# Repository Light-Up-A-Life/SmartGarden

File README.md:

# SmartGarden
Smart Garden development for the Light Up A Life project

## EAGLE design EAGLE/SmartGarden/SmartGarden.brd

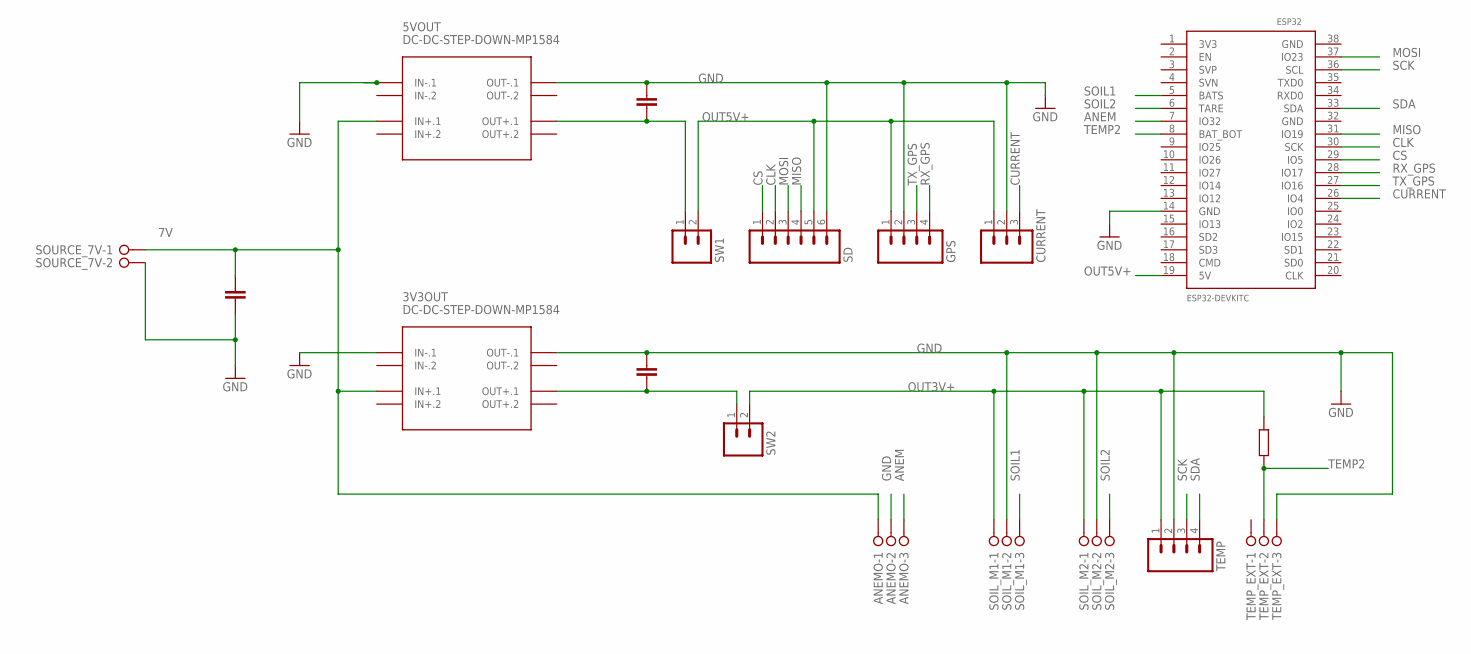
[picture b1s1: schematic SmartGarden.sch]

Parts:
3V3OUT, 5VOUT: DC-DC-STEP-DOWN-MP1584
ANEMO: W237-3E
C3V, C5V, C7V: C-EU025-025X050; C025-025X050
CURRENT: M03; 03P
ESP32: ESP32DEVKITC; ESP32-DEVKITC
GPS: M04; 04P
R1: R-EU_0204/7; 0204/7
SD: M06; 06P
SOIL_M1, SOIL_M2: W237-3E
SOURCE_7V: W237-02P; W237-132
SW1, SW2: M02; 02P
TEMP: M04; 04P
TEMP_EXT: W237-3E

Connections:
7V: 3V3OUT.IN+.1, 5VOUT.IN+.1, ANEMO.1, C7V.1, SOURCE_7V.1
ANEM: ANEMO.3, ESP32.7 (IO32)
CLK: ESP32.30 (SCK), SD.2
CS: ESP32.29 (IO5), SD.1
CURRENT: CURRENT.3, ESP32.26 (IO4)
GND: 3V3OUT.IN-.1, 3V3OUT.OUT-.1, 5VOUT.IN-.1, 5VOUT.OUT-.1, ANEMO.2, C3V.1, C5V.1, C7V.2, CURRENT.2, ESP32.14 (GND), GPS.2, SD.6, SOIL_M1.2, SOIL_M2.2, SOURCE_7V.2, TEMP.2, TEMP_EXT.3
MISO: ESP32.31 (IO19), SD.4
MOSI: ESP32.37 (IO23), SD.3
unnamed: 3V3OUT.OUT+.1, C3V.2, SW2.1
unnamed: 5VOUT.OUT+.1, C5V.2, SW1.1
OUT3V+: R1.2, SOIL_M1.1, SOIL_M2.1, SW2.2, TEMP.1
OUT5V+: CURRENT.1, ESP32.19 (5V), GPS.1, SD.5, SW1.2
RX_GPS: ESP32.28 (IO17), GPS.4
SCK: ESP32.36 (SCL), TEMP.3
SDA: ESP32.33 (SDA), TEMP.4
SOIL1: ESP32.5 (BATS), SOIL_M1.3
SOIL2: ESP32.6 (TARE), SOIL_M2.3
TEMP2: ESP32.8 (BAT_BOT), R1.1, TEMP_EXT.2
TX_GPS: ESP32.27 (IO16), GPS.3

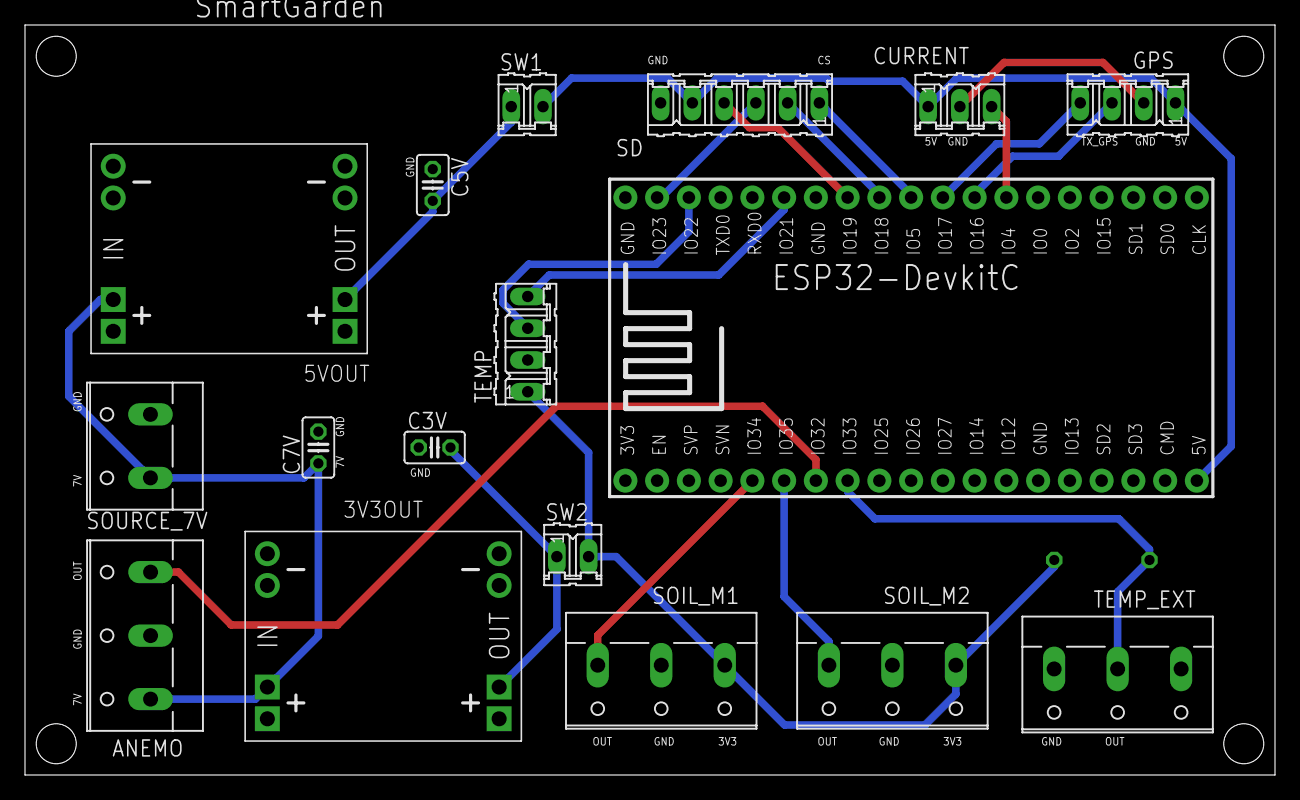
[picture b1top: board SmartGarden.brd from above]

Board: 2 copper layers, 100.0 x 60.0 mm, 18 parts (1 on the bottom side), 19 nets.

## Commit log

2020-10-14 Reorganization and adding of old Arduino tests
2020-10-14 Deleting hidden files
2020-10-14 Adding the .gitignore
2020-10-15 Solve problem with SD Adapter for Arduino
2020-10-16 sd esp32 works
2020-10-21 Several changes
    Changes on
    - the main cpp for SD card and GSM
    - platformio.ini
    - add of the test files for GSM module
2020-10-25 Time and gps working
2020-11-14 Correction in merging versions fixed
2020-11-15 Created message when SD card is removed
2021-01-31 Changes with Jose for checking on the overall system
    SD card working
    Unitary test for sensors.
    - BMP works
    - DS temp doesnt
    GSM to be checked!
2021-02-13 Update of unitary tests and integration of GSM working
2021-02-13 Version to work on !!
    Latest updated version with overall changes
2021-02-13 Addition of the EAGLE files
    Addition of the EAGLE files
2021-03-02 Create initial schematic in EAGLE
2021-04-26 Board impress v1 ... problem with the model ESP32
2021-04-28 Fix errors in PCB, added capacitors and holes
2021-04-28 Transition to class ... working with temp
2021-05-18 feat: GSM module working in main class TODO: clear cpp file
2021-05-18 refactor: Delete libraries, include in the plataformio.init, derivate constructor from Sensor class
2021-06-08 Add unit test to bmp sensor --> moving include to lib to execute tests
2021-08-08 Separate clock and read sensors in task threads
2021-09-26 Added soil moisture sensor
2021-10-27 Threading working clock and callbacks
2021-11-01 Adding the Display class
    Adding the Display class with the integration within the main code
2021-11-17 Display done :)
2021-11-17 Update on the logo
    Update on the logo
2021-11-22 Add sd apend event each minute, add lib bme280
2021-11-24 Initial test module sim 7600
2021-12-05 Working with google sheets
2021-12-05 Integrate wifi connection and google sheets writing
2021-12-07 Added External temp and anemometer
2021-12-09 Comm sms and socket zorking zit AT
2021-12-09 Release Colombia
2021-12-11 Update eagle
2021-12-12 Json Format message
2022-01-28 Cambios La Guajira
2022-02-06 Fix merge problems
2022-02-08 Added main document (uml/schematic)

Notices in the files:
parts and their libraries:
diy-modules: Released under the Creative Commons Attribution 4.0 International License: http://creativecommons.org/licenses/by/4.0
